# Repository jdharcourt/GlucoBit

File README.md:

# GlucoBit

A CircuitPython glucose monitoring display that fetches readings from the Dexcom Share API and shows them on a colour LCD. Plays audio alarms and flashes an LED when glucose goes out of range.

**Current version:** 1.2.2

## About

GlucoBit is a standalone glucose visualisation and alert device. The product aims to solve some of the daily issues faced by Type 1 Diabetics. At present, CGMs (Continuous Glucose Monitors) send glucose data to a smartphone, where the user can access their current levels and receive alerts for low and high blood sugar events, however, missed hypoglycemic alarms, alarm fatigue, and an over-reliance on smartphones for blood glucose monitoring can cause huge issues for people with type 1 Diabetes.

One of the biggest issues faced with traditional phone-based glucose monitoring is the over-reliance on smartphones. GlucoBit solves this problem by providing a standalone, fully battery-powered device that can travel with you, displaying current glucose levels on an Always-on-display, along with glucose range indicating LEDs. The versatility of GlucoBit allows it to be used anywhere, whether that be on a bedside table, a desk at school or work, or even in an exam situation where phones for glucose monitoring and alerts are not allowed.

Also, smartphone-provided low glucose alerts are often reported to be too quiet and short to effectively alert the user, particularly when sleeping. GlucoBit addresses this problem by providing a louder, persistent alarm that continues until silenced by the user, ensuring they have been alerted to their critical glucose event.

## Hardware

| Component | Details |
|-----------|---------|
| Display | ST7789 SPI, 280×240, rotated 90° |
| Audio | I2S speaker, plays `audio/basic.wav` for alarms |
| Touch | Capacitive sensor on A2 — wake from sleep / silence alarm |
| LED | Neopixel for glucose-level colour feedback |
| Battery | ADC for voltage and percentage |

## Features

- Fetches glucose readings every 90 seconds from the Dexcom cloud API
- Three display themes (card, split-band, minimal)
- Low / high / very-high alarms with audio and LED
- Touch-to-silence alarm
- Web UI for configuration (connect to device IP on port 80)
- Bluetooth setup and settings via the iOS companion app (see [`ios/`](ios/README.md))
- BLE reading relay: the iOS app pushes Dexcom readings to the device when its WiFi is down
- OTA updates via GitHub Releases (checked hourly)
- Deep sleep between fetches to conserve battery

## Alarm Thresholds

| Level | mmol/L | mg/dL |
|-------|--------|-------|
| Low | < 3.9 | < 70 |
| High | > 10.0 | > 180 |
| Very High | > 13.0 | > 250 |

## Setup

1. Flash CircuitPython to your board.
2. Copy all files from this repo to the `CIRCUITPY` drive (excluding `lib/` — install Adafruit libraries separately).
3. Create `settings.json` on the device:

```json
{
  "WIFI_SSID": "your_ssid",
  "WIFI_PASSWORD": "your_password",
  "DEXCOM_USERNAME": "your_dexcom_email",
  "DEXCOM_PASSWORD": "your_dexcom_password",
  "DEXCOM_SERVER": "shareous1.dexcom.com",
  "DISPLAY_NAME": "Name",
  "BACKGROUND_COLOR": "000000",
  "MMOL": true,
  "UI_THEME": 1,
  "SETUP_MODE": false
}
```

> Use `"shareous1.dexcom.com"` for US accounts or `"share2.dexcom.com"` for international.

4. Power on — the device connects to WiFi and starts fetching readings.

## Web UI

Navigate to the device's IP address in a browser to update settings without re-flashing. Changes take effect immediately.

## File Structure

```
firmware/code.py         Entry point
firmware/app/main.py     All application logic
firmware/app/ble.py      BLE GATT server for the iOS companion app
firmware/boot.py         Remounts filesystem read-write on device
firmware/wifi.py         WiFi connection helpers
firmware/ota.py          OTA update system
firmware/audio/          Alarm sound
firmware/icons/          Trend arrow bitmaps
firmware/fonts/          Nunito BDF fonts (30pt, 40pt, 80pt)
hardware/                KiCad PCB design (ESP32-S3-WROOM-1)
ios/                     iOS companion app (SwiftUI) — see ios/README.md
```

BLE requires CircuitPython ≥ 9.0 on the device (`_bleio` on ESP32-S3). On
older builds the firmware logs "BLE unavailable" and runs WiFi-only.

## Filesystem Note

`boot.py` remounts the filesystem read-write for the device, which makes the `CIRCUITPY` drive read-only from the Mac. To write from the Mac (e.g. to edit files), hold the designated GPIO button on boot to skip the remount.

## OTA Updates

Updates are published as GitHub Releases. The device checks for a new version every hour, downloads to `/_update/`, and reboots automatically.

## License

MIT

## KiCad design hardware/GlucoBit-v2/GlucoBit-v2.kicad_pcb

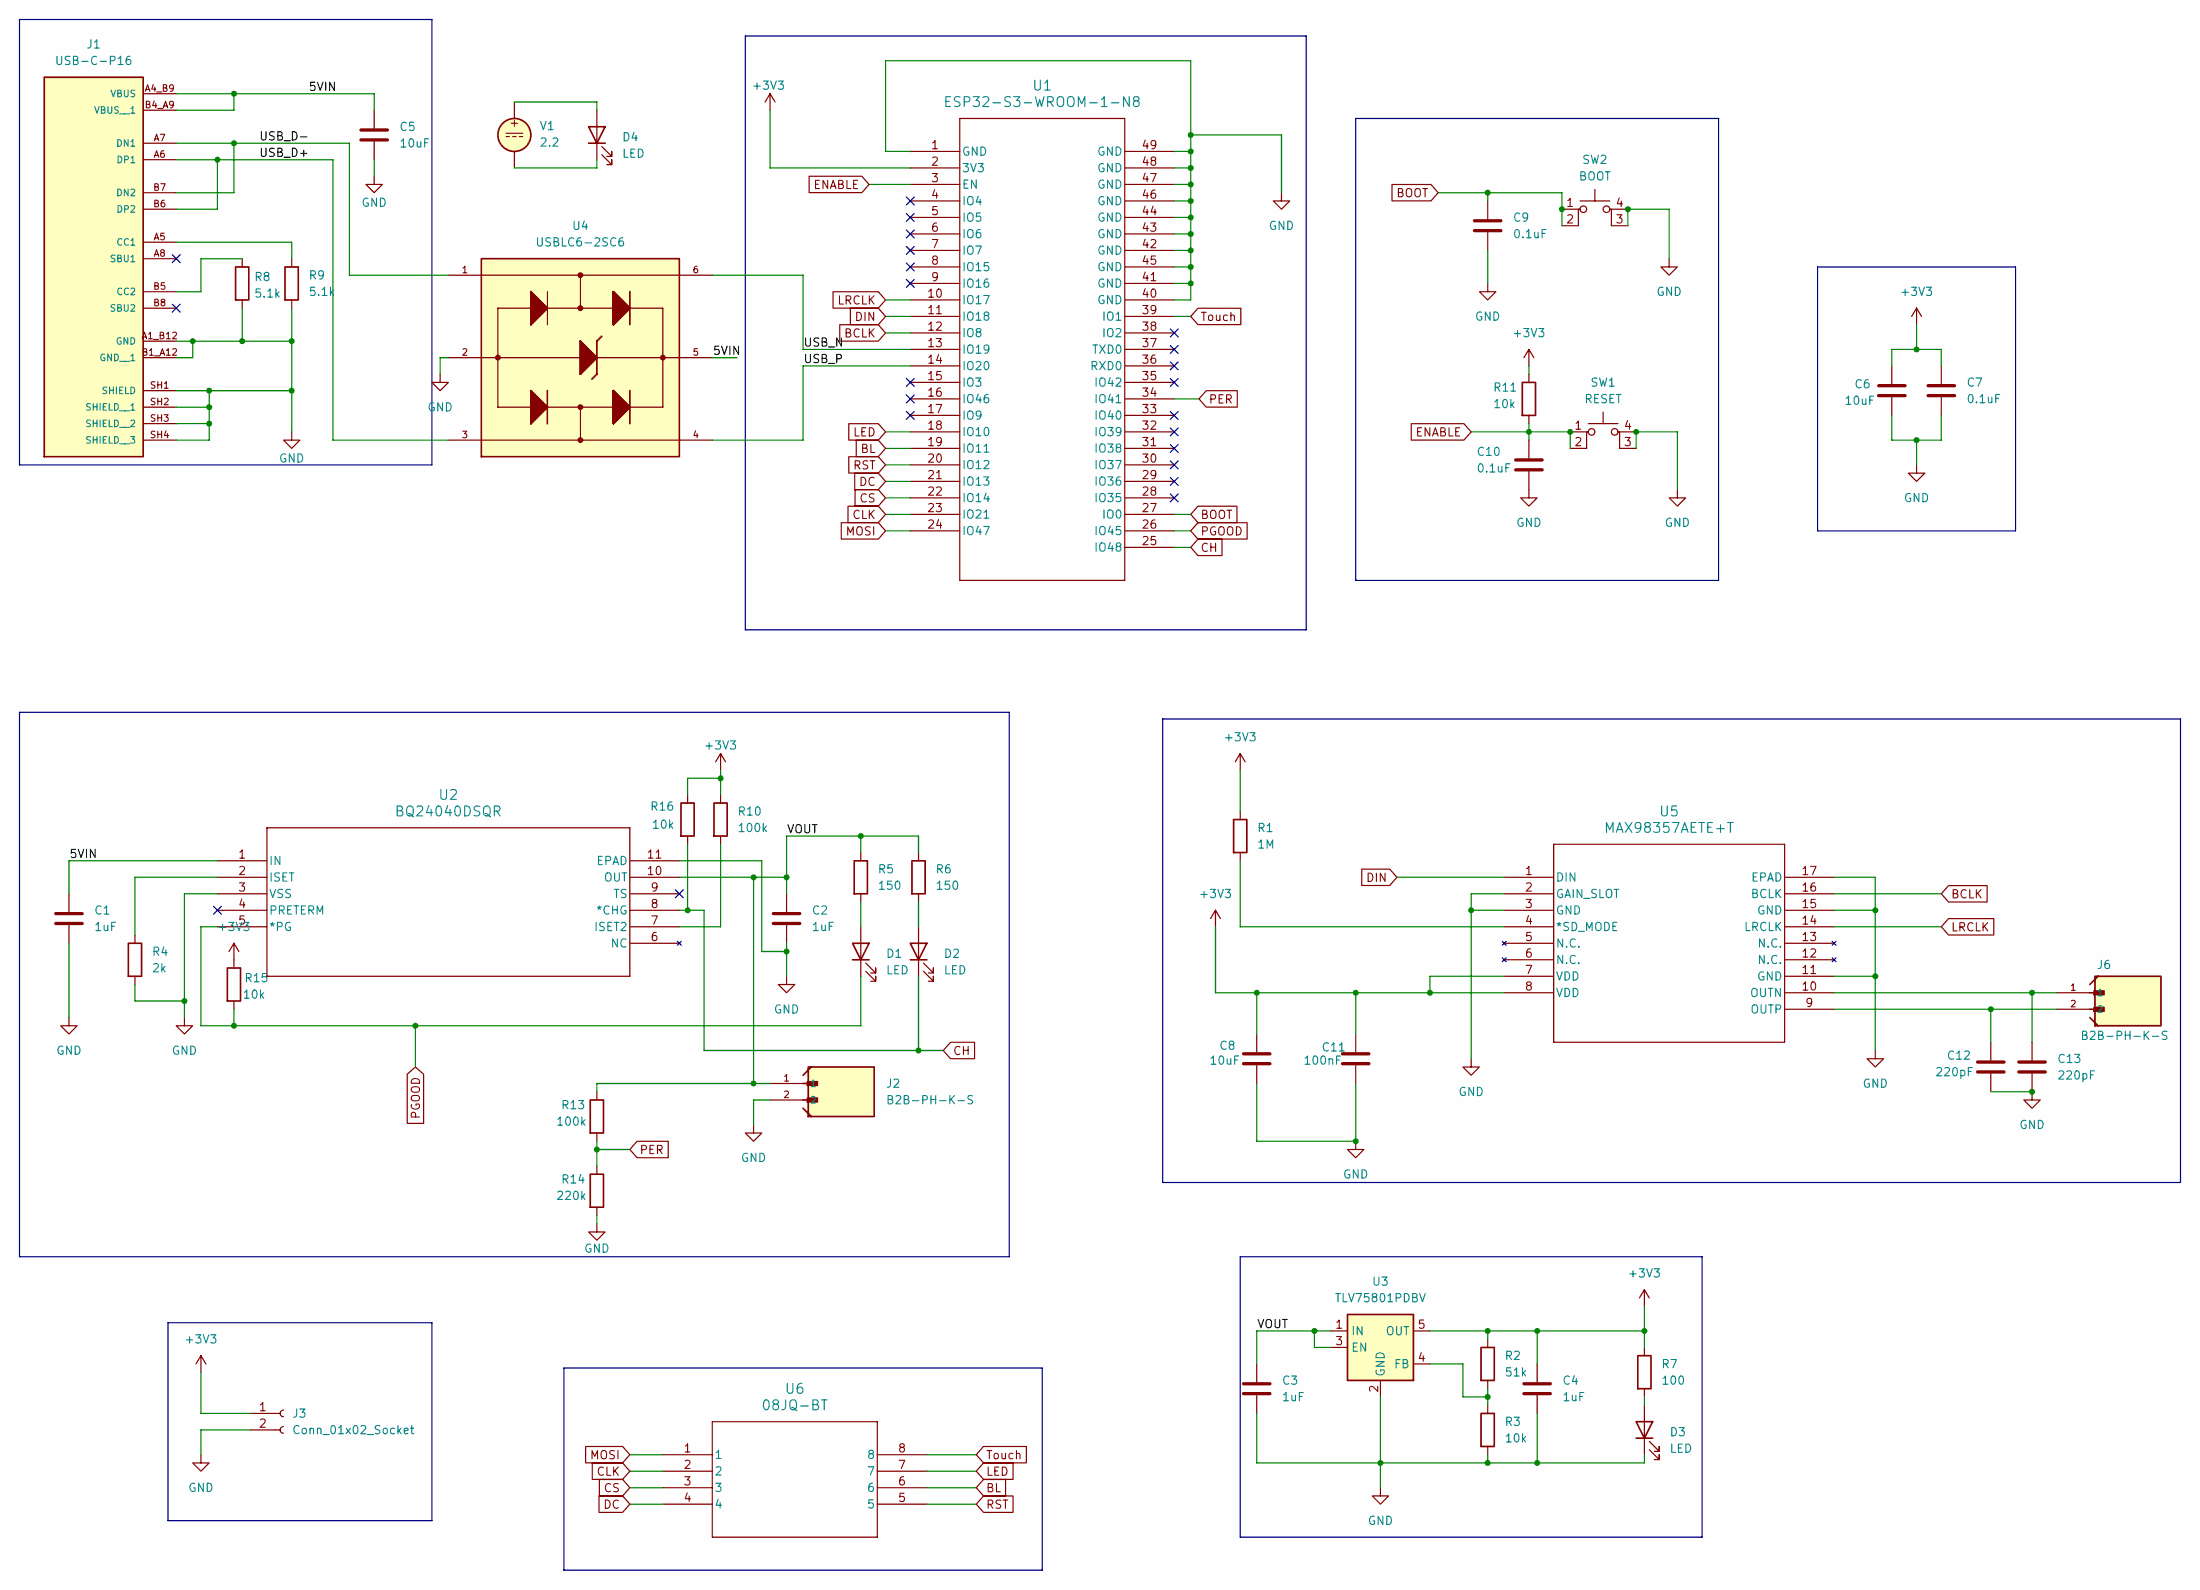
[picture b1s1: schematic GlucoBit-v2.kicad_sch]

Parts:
C1, C2: 1uF; C_0805_2012Metric
C3, C4: 1uF; R_0603_1608Metric
C5: 10uF; C_0805_2012Metric
C6, C8: 10uF; C_1206_3216Metric
C7: 0.1uF; C_0603_1608Metric
C9, C10: 0.1uF; C_0805_2012Metric
C11: 100nF; C_0603_1608Metric
C12, C13: 220pF; C_0603_1608Metric
D1, D2, D3, D4: LED; LED_0805_2012Metric
J1: USB-C-P16; PARTREV 1.0
J2, J6: B2B-PH-K-S; JST_B2B-PH-K-S
J3: Conn_01x02_Socket; PinSocket_1x02_P2.54mm_Vertical
R1: 1M; R_0603_1608Metric
R2: 51k; R_0603_1608Metric
R3, R11, R15, R16: 10k; R_0603_1608Metric
R4: 2k; R_0603_1608Metric
R5, R6: 150; R_0603_1608Metric
R7: 100; R_0603_1608Metric
R8, R9: 5.1k; R_0603_1608Metric
R10, R13: 100k; R_0603_1608Metric
R14: 220k; R_0603_1608Metric
SW1: RESET; PTS810_CNK
SW2: BOOT; PTS810_CNK
U1: ESP32-S3-WROOM-1-N8; ESP32-S3-WROOM-1
U2: BQ24040DSQR; DSQ10_P9X1P5
U3: TLV75801PDBV; SOT-23-5
U4: USBLC6-2SC6; SOT95P280X145-6N
U5: MAX98357AETE+T; DAC
U6: 08JQ-BT; JSTx8
V1: 2.2

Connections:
+3V3: C4.1, C6.1, C7.1, C8.1, C11.1, J3.1, R1.1, R2.1, R7.1, R10.1, R11.1, R15.1, R16.1, U1.2 (3V3), U3.5 (OUT), U5.7 (VDD), U5.8 (VDD)
/5VIN: C1.1, C5.1, J1.A4_B9 (VBUS), J1.B4_A9 (VBUS__1), U2.1 (IN), U4.5
/USB_D+: J1.A6 (DP1), J1.B6 (DP2), U4.3
/USB_D-: J1.A7 (DN1), J1.B7 (DN2), U4.1
/USB_N: U1.13 (IO19), U4.6
/USB_P: U1.14 (IO20), U4.4
/VOUT: C2.1, C3.1, J2.1, R5.1, R6.1, R13.1, U2.10 (OUT), U3.1 (IN), U3.3 (EN)
BCLK: U1.12 (IO8), U5.16 (BCLK)
BL: U1.19 (IO11), U6.6
BOOT: C9.1, SW2.1, SW2.2, U1.27 (IO0)
CH: D2.1 (K), R16.2, U1.25 (IO48), U2.8 (*CHG)
CLK: U1.23 (IO21), U6.2
CS: U1.22 (IO14), U6.3
DC: U1.21 (IO13), U6.4
DIN: U1.11 (IO18), U5.1 (DIN)
ENABLE: C10.1, R11.2, SW1.1, SW1.2, U1.3 (EN)
GND: C1.2, C2.2, C3.2, C4.2, C5.2, C6.2, C7.2, C8.2, C9.2, C10.2, C11.2, C12.2, C13.2, D3.1 (K), J1.A1_B12 (GND), J1.B1_A12 (GND__1), J1.SH1 (SHIELD), J1.SH2 (SHIELD__1), J1.SH3 (SHIELD__2), J1.SH4 (SHIELD__3), J2.2, J3.2, R3.2, R4.2, R8.2, R9.2, R14.2, SW1.3 (K), SW1.4 (A), SW2.3 (K), SW2.4 (A), U1.1 (GND), U1.40 (GND), U1.41 (GND), U1.42 (GND), U1.43 (GND), U1.44 (GND), U1.45 (GND), U1.46 (GND), U1.47 (GND), U1.48 (GND), U1.49 (GND), U2.3 (VSS), U2.11 (EPAD), U2.V, U3.2 (GND), U4.2, U5.2 (GAIN_SLOT), U5.3 (GND), U5.11 (GND), U5.15 (GND), U5.17 (EPAD)
LED: U1.18 (IO10), U6.7
LRCLK: U1.10 (IO17), U5.14 (LRCLK)
MOSI: U1.24 (IO47), U6.1
unnamed: D1.2 (A), R5.2
unnamed: D2.2 (A), R6.2
unnamed: D3.2 (A), R7.2
unnamed: D4.1 (K), V1.2
unnamed: D4.2 (A), V1.1
unnamed: J1.A5 (CC1), R9.1
unnamed: J1.B5 (CC2), R8.1
unnamed: R10.2, U2.7 (ISET2)
unnamed: R4.1, U2.2 (ISET)
unnamed: R2.2, R3.1, U3.4 (FB)
unnamed: R1.2, U5.4 (*SD_MODE)
unnamed: C13.1, J6.1, U5.10 (OUTN)
unnamed: C12.1, J6.2, U5.9 (OUTP)
PER: R13.2, R14.1, U1.34 (IO41)
PGOOD: D1.1 (K), R15.2, U1.26 (IO45), U2.5 (*PG)
RST: U1.20 (IO12), U6.5
Touch: U1.39 (IO1), U6.8

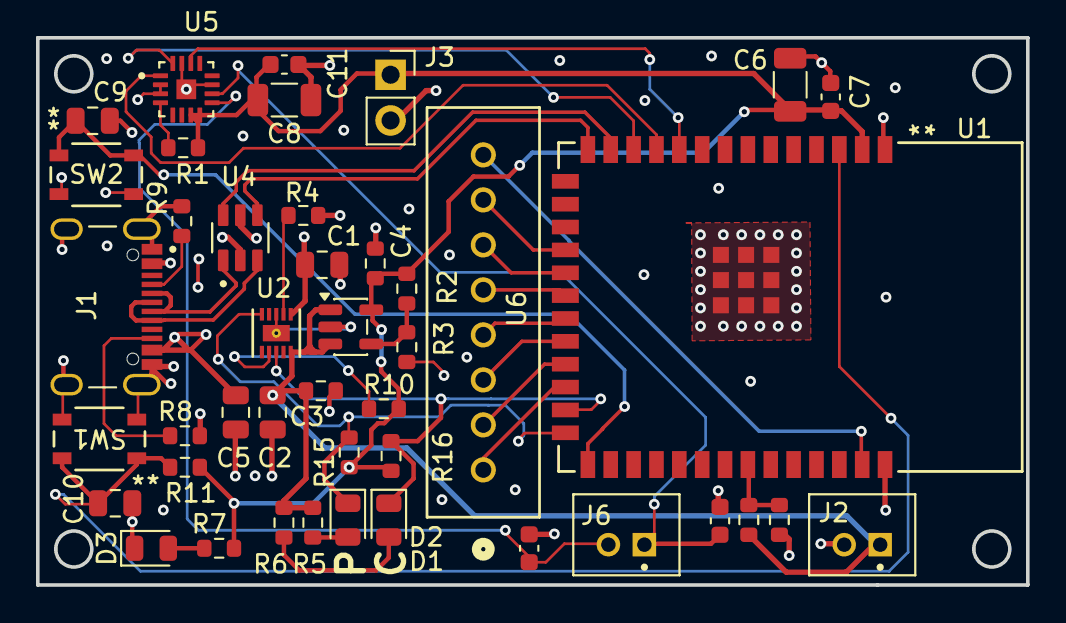
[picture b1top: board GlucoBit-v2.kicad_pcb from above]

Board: 4 copper layers, 55.0 x 30.4 mm, 43 parts (0 on the bottom side), 35 nets.

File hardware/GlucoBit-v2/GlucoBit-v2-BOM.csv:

#,References,Qty,Value,Footprint,MPN,Manufacturer,Description,Unit Price,Ext. Price,Stock,Supplier P/N,Datasheet,Buy Link,DNP
1,"C1, C2",2,1uF,C_0805_2012Metric,CL05B104KP5NNNC,Samsung Electro-Mechanics,CAP CER 0.1UF 10V X7R 0402,0.1000,0.20,27468402,1276-1002-2-ND,https://mm.digikey.com/Volume0/opasdata/d220001/medias/docus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,https://www.digikey.com/en/products/detail/samsung-electro-m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,
2,"C3, C4",2,1uF,R_0603_1608Metric,CL05B104KP5NNNC,Samsung Electro-Mechanics,CAP CER 0.1UF 10V X7R 0402,0.1000,0.20,27468402,1276-1002-2-ND,https://mm.digikey.com/Volume0/opasdata/d220001/medias/docus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,https://www.digikey.com/en/products/detail/samsung-electro-m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,
3,C5,1,10uF,C_0805_2012Metric,GRM155R60J106ME05D,Murata Electronics,CAP CER 10UF 6.3V X5R 0402,0.1000,0.10,766794,490-GRM155R60J106ME05DTR-ND,https://search.murata.co.jp/Ceramy/image/img/A01X/G101/ENG/G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,https://www.digikey.com/en/products/detail/murata-electronic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,
4,"C6, C8",2,10uF,C_1206_3216Metric,GRM155R60J106ME05D,Murata Electronics,CAP CER 10UF 6.3V X5R 0402,0.1000,0.20,766794,490-GRM155R60J106ME05DTR-ND,https://search.murata.co.jp/Ceramy/image/img/A01X/G101/ENG/G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,https://www.digikey.com/en/products/detail/murata-electronic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,
5,C7,1,0.1uF,C_0603_1608Metric,CL05B104KP5NNNC,Samsung Electro-Mechanics,CAP CER 0.1UF 10V X7R 0402,0.1000,0.10,27468402,1276-1002-2-ND,https://mm.digikey.com/Volume0/opasdata/d220001/medias/docus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,https://www.digikey.com/en/products/detail/samsung-electro-m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,
6,"C9, C10",2,0.1uF,C_0805_2012Metric,CL05B104KP5NNNC,Samsung Electro-Mechanics,CAP CER 0.1UF 10V X7R 0402,0.1000,0.20,27468402,1276-1002-2-ND,https://mm.digikey.com/Volume0/opasdata/d220001/medias/docus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,https://www.digikey.com/en/products/detail/samsung-electro-m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,
7,C11,1,100nF,C_0603_1608Metric,CL10E104KC8VPNC,Samsung Electro-Mechanics,CAP CER 100NF 100V X8L 0603,0.2700,0.27,445616,1276-CL10E104KC8VPNCTR-ND,https://mm.digikey.com/Volume0/opasdata/d220001/medias/docus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,https://www.digikey.com/en/products/detail/samsung-electro-m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,
8,"C12, C13",2,220pF,C_0603_1608Metric,C0603C221K5RACTU,KEMET,CAP CER 220PF 50V X7R 0603,0.1000,0.20,933138,399-C0603C221K5RACTUTR-ND,https://yageogroup.com/content/datasheet/asset/file/KEM_C100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,https://www.digikey.com/en/products/detail/kemet/C0603C221K5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,
9,"D1, D2, D3, D4",4,LED,LED_0805_2012Metric,UHD111A-FKA-C3K23E1L3VG5ZB3Z3,Cree LED,LED RGB 0404 SMD,0.1000,0.40,147266,90-UHD111A-FKA-C3K23E1L3VG5ZB3Z3-ND,https://downloads.cree-led.com/files/ds/h/HB-UHD111A-FKA.pdf,https://www.digikey.com/en/products/detail/cree-led/UHD111A-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,
10,J1,1,USB-C-P16,USB-C-P16,,,,,,,,,,
11,"J2, J6",2,B2B-PH-K-S,JST_B2B-PH-K-S,B2B-PH-K-S,JST Sales America Inc.,CONN HEADER VERT 2POS 2MM,0.1100,0.22,19463,455-1704-ND,https://www.jst-mfg.com/product/pdf/eng/ePH.pdf,https://www.digikey.com/en/products/detail/jst-sales-america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,
12,J3,1,Conn_01x02_Socket,PinSocket_1x02_P2.54mm_Vertical,,,,,,,,,,
13,R1,1,1M,R_0603_1608Metric,RC0402FR-071ML,YAGEO,RES 1M OHM 1% 1/16W 0402,0.1000,0.10,2066587,311-1.00MLRTR-ND,https://yageogroup.com/content/datasheet/asset/file/PYU-RC_G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,https://www.digikey.com/en/products/detail/yageo/RC0402FR-07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,
14,R2,1,51k,R_0603_1608Metric,CRCW08051K00FKEA,Vishay Dale,RES SMD 1K OHM 1% 1/4W 0805,0.1000,0.10,1066635,541-1.00KCTR-ND,https://www.vishay.com/docs/20035/dcrcwe3.pdf,https://www.digikey.com/en/products/detail/vishay-dale/CRCW0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,
15,"R3, R11, R15, R16",4,10k,R_0603_1608Metric,RC0603FR-0710KL,YAGEO,RES 10K OHM 1% 1/10W 0603,0.1000,0.40,12267747,311-10.0KHRTR-ND,https://yageogroup.com/content/datasheet/asset/file/PYU-RC_G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,https://www.digikey.com/en/products/detail/yageo/RC0603FR-07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,
16,R4,1,2k,R_0603_1608Metric,RC0402FR-072KL,YAGEO,RES 2K OHM 1% 1/16W 0402,0.1000,0.10,2216148,311-2KLRTR-ND,https://yageogroup.com/content/datasheet/asset/file/PYU-RC_G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,https://www.digikey.com/en/products/detail/yageo/RC0402FR-07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,
17,"R5, R6",2,150,R_0603_1608Metric,150,Keystone Electronics,BATT HOLDER C 3 CELL SOLDER LUG,12.1000,24.20,279,36-150-ND,https://www.keyelco.com/userAssets/file/K75p23.pdf,https://www.digikey.com/en/products/detail/keystone-electron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,
18,R7,1,100,R_0603_1608Metric,100,Keystone Electronics,BATT CONTACT CLIP AA SOLDER LUG,1.2900,1.29,1001,36-100-ND,https://www.keyelco.com/userAssets/file/K75p22.pdf,https://www.digikey.com/en/products/detail/keystone-electron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,
19,"R8, R9",2,5.1k,R_0603_1608Metric,ERJ-2RKF5101X,Panasonic Industry,RES SMD 5.1K OHM 1% 1/10W 0402,0.1000,0.20,738587,P5.10KLTR-ND,https://industrial.panasonic.com/cdbs/www-data/pdf/RDA0000/A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,https://www.digikey.com/en/products/detail/panasonic-industr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,
20,"R10, R13",2,100k,R_0603_1608Metric,RC0402FR-07100KL,YAGEO,RES 100K OHM 1% 1/16W 0402,0.1000,0.20,12945540,311-100KLRTR-ND,https://yageogroup.com/content/datasheet/asset/file/PYU-RC_G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,https://www.digikey.com/en/products/detail/yageo/RC0402FR-07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,
21,R14,1,220k,R_0603_1608Metric,CRCW040220K0FKED,Vishay Dale,RES 20K OHM 1% 1/16W 0402,0.1000,0.10,923985,541-20.0KLTR-ND,https://www.vishay.com/docs/20035/dcrcwe3.pdf,https://www.digikey.com/en/products/detail/vishay-dale/CRCW0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,
22,SW1,1,RESET,PTS810_CNK,NC7SZ175P6X,onsemi,IC FF D-TYPE SINGLE 1BIT SC-88,0.1000,0.10,142234,NC7SZ175P6XTR-ND,https://www.onsemi.com/pub/Collateral/NC7SZ175-D.PDF,https://www.digikey.com/en/products/detail/onsemi/NC7SZ175P6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,
23,SW2,1,BOOT,PTS810_CNK,PD-CAP-1/8-0,TE Connectivity Raychem Cable Protection,HEATSHRINK CAP BLACK,0.1700,0.17,22435,PDC018K-ND,https://www.te.com/commerce/DocumentDelivery/DDEController?A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,https://www.digikey.com/en/products/detail/te-connectivity-r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,
24,U1,1,ESP32-S3-WROOM-1-N8,ESP32-S3-WROOM-1,ESP32-S3-WROOM-1-N8,Espressif Systems,RF TXRX MODULE WIFI PCB TRACE,5.6600,5.66,3012,5407-ESP32-S3-WROOM-1-N8TR-ND,https://www.espressif.com/sites/default/files/documentation/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,https://www.digikey.com/en/products/detail/espressif-systems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,
25,U2,1,BQ24040DSQR,DSQ10_P9X1P5,BQ24040DSQR,Texas Instruments,IC BATT CHG LI-ION 1CELL 10SON,0.9500,0.95,25428,296-37142-2-ND,https://www.ti.com/lit/ds/symlink/bq24040.pdf,https://www.digikey.com/en/products/detail/texas-instruments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,
26,U3,1,TLV75801PDBV,SOT-23-5,TLV75801PDBVR,Texas Instruments,IC REG LIN POS ADJ 500MA SOT23-5,0.3100,0.31,60801,296-TLV75801PDBVRTR-ND,https://www.ti.com/general/docs/suppproductinfo.tsp?distId=1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,https://www.digikey.com/en/products/detail/texas-instruments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,
27,U4,1,USBLC6-2SC6,SOT95P280X145-6N,USBLC6-2SC6,"Shenzhen Slkormicro Semicon Co., Ltd.",6A@8/20US 13V 78W@8/20US 9V 5V S,0.1700,0.17,12024,5399-USBLC6-2SC6TR-ND,https://mm.digikey.com/Volume0/opasdata/d220001/medias/docus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,https://www.digikey.com/en/products/detail/shenzhen-slkormic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,
28,U5,1,MAX98357AETE+T,DAC,MAX98357AETE+T,Analog Devices Inc./Maxim Integrated,IC AMP CLASS D MONO 3.2W 16TQFN,3.7300,3.73,22470,MAX98357AETE+TTR-ND,https://datasheets.maximintegrated.com/en/ds/MAX98357A-MAX98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,https://www.digikey.com/en/products/detail/analog-devices-in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,
29,U6,1,08JQ-BT,JSTx8,08JQ-BT,JST Sales America Inc.,CONN RCPT 8POS 0.098 TIN PCB,0.5100,0.51,892,455-2970-ND,https://www.jst-mfg.com/product/pdf/eng/eJQ.pdf,https://www.digikey.com/en/products/detail/jst-sales-america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,
30,V1,1,2.2,,T18S9M4,HellermannTyton,"CBL TIE LOCKING NAT 18LB 3.27""",0.0232,0.02,57900,1436-1516-ND,https://assets.hellermanntyton.us/m/2164f83b29279c64/origina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,https://www.digikey.com/en/products/detail/hellermanntyton/T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,

,TOTAL,45,,,,,,,40.40

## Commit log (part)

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2025-09-24 Added primary files and folders - v1
2026-01-05 Added new libraries
2026-01-05 Added new library folders
    Added the following libraries to /lib/ -
    Adafruit Colorsys
    Adafruit Imageload
    Adafruit Wiznet
2026-01-05 Uploaded revised trend arrow icons
2026-01-05 Delete backup.py
    Deleted unnecessary backup code file
2026-01-05 Refactor touch and alarm handling with color updates
    Altered touch initialisation and alarm handling, improve color handling for glucose display, and enhance sleep functionality.
2026-01-05 Rename boot.bak to boot.py
2026-01-05 Created README.MD
2026-01-05 Revise README for GlucoBit device details
    Updated README to reflect changes in device features, hardware requirements, and setup instructions.
2026-01-06 Revise Dexcom server info and contribution guidelines
    Updated server addresses and modified contributing section for clarity.
2026-01-19 Revise enclosure section in README
    Updated the enclosure section with a new heading and added an image for the 3D model.
2026-01-19 Update README to include image instead of link
    Replaced a link with an image for better visual representation.
2026-02-06 Refactor main execution and import structure
    Refactor code structure and update main execution flow.
2026-02-06 added /app/~ file route and additional app code
    restructured overall app structure using code.py that runs /app/main.py
2026-03-18 Add Google site verification to README
    Added Google site verification meta tag to README.
2026-03-18 Remove Google site verification from README
    Removed Google site verification meta tag from README.
2026-03-18 Add Google site verification to README
    Added Google site verification file reference to README.
2026-03-18 Remove Google site verification information
    Removed Google site verification details from README.
2026-03-21 Complete restructure to allow for OTA updates.
2026-06-10 Add PCB files to hardware dir
2026-06-11 Create basis for compainion app and integrate bluetooth data feature
2026-06-12 Finished Routing PCB, ready for DFM
2026-06-13 Ran Local DFM, ready for offical DFM
2026-06-13 Update PCB after DFM
2026-06-13 Syncyed KiCad Files, Created initail Gerbers for DFM
2026-06-13 Ran initial DFM, Updated routing + gerbers
2026-06-13 Ran #2 DFM, Updated routing + gerbers
2026-06-14 Update UI
2026-06-14 Feat - Edit Device settings in app
2026-06-14 Replaced traditional data retrival polling with new method to remove stale data
2026-06-14 Updated app UI
2026-06-14 Recreate Gauge to cohere with design rules. Make home page non scrollable
2026-06-14 Feat - add future potential for critical alert notifications. (Apple Dev approval req)
2026-06-14 Feat - Hover gesture on graph, precise blood glucose shown
2026-06-18 Generated STEP files
2026-06-18 add usb-c model
2026-06-18 add usb-c model to pcb step
2026-06-19 Add BLE WiFi scanning and smoother display updates
2026-06-19 Edged edge case for stale data on line graph. Feat + added vibrate on hover
2026-06-19 Feat+Bug Added Developer mode to ios app and firmware Fixed Alarm sliders
2026-06-19 Automatic timezone detection, config setting in app and ap
2026-06-19 Add changelog dialogue to release.sh
2026-06-22 Update README.md with about section
2026-06-22 Fix README.md
2026-06-22 Fix about heading - README.md
